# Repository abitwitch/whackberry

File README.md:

# WhackberryPi
Disconnected Cyberdeck for password management.

## Features:
- Disconnected computer (with display) with no wireless connectivity on any part of the device
- QWERTY keyboard with access to most standard symbols
- A mouse for navigating the OS in GUI mode
- A additional Micro SD card reader that can be used to create backups of passwords for storage in a secure secondary location
- A Camera to take pictures that are unable to reach the internet (useful for QR backup codes of 2FA apps)
- A disconnected microcontroller that is able to transmit data from the disconnected computer to another computer using a data diode

## How the data diode works:
1. The disconnected computer has a special command for transmitting data (`ir-sender`). This program can take standard input in bash.
2. The program encrypts the input. *NOTE* that the hardware only suport very weak and out-of-date encryption. Although it may provide a small layer of security, it should not be relied upon. This means anyone able to read the IR led blinking from inside the case, may be able to eventually decypt the messages. This seems like a low-level risk.
3. The program break the message into packets then into pulses and used the IR LED light transmit the password. Since there is no way to read messages from the LED, this is a one way communication. This is the data diode and it uses the "fire and forget" principle. This means errors in reading the message is possible. A check sum is part of the protocol to account for this possible error.
4. On the other side of the LED there is a IR Reciever. It is connected to a microcontroller that is completely disconnected* from the raspberry PI. The only way to communicate is over the air-gap via IR (one way).
*Note that the microcontroller is connected via power (5v and Ground). This allows the disconnected computer to be powered when the microcontroller is pluged into a computer. This does technically open the possibility of side channel attacks. 
5. The signal is recieved, decapsulated, combined, and de-crypted. The checksum is verified before decryption and the process will only continue if the checksum and decryption are successful.
6. When plugged into a computer, the air-gapped microcontroller acts as a keyboard and the message recieved is transmitted as keystrokes to the computer.

# Setup:
To set up a device, follow the instructions in each section of this readme from top to bottom. 

## Main Hardware
- Raspberry Pi Zero v1.3 [link](https://www.adafruit.com/product/2885)
- M5 CardKB (v1.1)
- HDMI 5" Display [link](https://www.adafruit.com/product/2232)
- Raspberry Pi Camera Module 3 [link](https://www.adafruit.com/product/5657)
- Infrared LED [link](https://www.adafruit.com/product/387)
- Infrared Receiver Sensor [link](https://www.adafruit.com/product/157)
- QT Py RP2040 [link](https://www.adafruit.com/product/4900)
- At least 1 micro CD card
- A Raspberry Pi with internet (for setup only)

## Supporting Hardware and PCB Mounting / cable accessories
- SMD Grove Female Header [link](https://www.mouser.ca/ProductDetail/Seeed-Studio/114020164?qs=7MVldsJ5Uayw%2FOfizq4F8w%3D%3D)
- USB Type-A Jack [link](https://www.mouser.ca/ProductDetail/Amphenol-FCI/87583-0010BHLF?qs=HGI6s9c03KdFNxR4%2F7F3Vg%3D%3D)
- HDMI cable [link1](https://www.adafruit.com/product/3552) [link2](https://www.adafruit.com/product/3549) [link3](https://www.adafruit.com/product/3561)
- Thru-hole 5-way Navigation switch (used as a mouse) [link](https://www.adafruit.com/product/504)
- 2x Buttons [link](https://www.adafruit.com/product/367)
- Pogo pins [link](https://www.adafruit.com/product/5381)
- Stand-off screws (the camera module may require a different size) [link](https://www.adafruit.com/product/3299)
- 1x 10k resistor [link](https://www.adafruit.com/product/2784)
- Male-male pin headers [link](https://www.adafruit.com/product/3009)
- USB Type C Breakout Board [link](https://www.adafruit.com/product/4090)
- SD card reader - SanDisk MobileMate USB 3.0 Reader [link](https://shop.sandisk.com/en-ca/products/accessories/memory-card-readers/sandisk-quickflow-microsd-usb-a-memory-card-reader?sku=SDDR-B731-GN6NN)
- DPDT switch [link](https://www.digikey.ca/en/products/detail/e-switch/EG2208/301963)
- One M4 nut and bolt (to attach CardKB)
- Solder and an soldering iron

## PCB
There PCB (Printed Circuit Board) design is included in this repository. This can be ordered online for a PCB manufacturer. If you want to forgo the case, you can order 2 boards and use the second with the one with standoffs to protect the device. 

**Schematic**

**Design view**

**Front view**

**Back view**

## Assembly guide

This guide assumes you have some experince with soldering. Locational references (up, down, left, right) assume the PCB is upright with the logo facing you. The logo side is the front of the board, the other side is the back. 
### Prepare parts
1. Break the Male-male pin headers into 2 7 pin pieces and 1 8 pin piece
2. Solder the QTpy to the two 7 pin headers with the pins facing away from the side with the USB port on it.
3. Repeat the previous step for the Raspberry Pi Zero, and USB-c Breakout board. 
4. Break the POGO pins into 2 single pins and 1 pieces with 2 still attatched pins.

### Attach USB-c Breakout board
1. Use a M2.5 hex nut as a space between the USB-c breakout board and the main PCB, with the USB-c breakour board on the back of the main PCB. Secure the breakout board in place with more M2.5 nuts and screws
2. Clip of excess pin length from the pins of the USB-c breakout board headers and then solder the pins in place

### Attach QTpy
1. Place the QTpy in place on the back of the main PCB
2. Clip of excess pin length from the pins of the QTpy headers and then solder the pins in place

### Attach Raspberry Pi Zero
1. Solder the 2 attached pogo pins below the main headed pins in the Raspberry Pi Zero footprint. The pins should be facing the back of the board
2. Use 6mm long F-F hex standoffs and screws to attach the Raspberry Pi Zero fo the back of the main PCB. The pogo pins should be making contect with the Raspberry Pi Zero, and the main header pins should slightly protrude through the main PCB. 
3. Solder all the main header pins into place.

### Other soldered-in pieces
1. Solder the GROVE Female Header onto the back of the main PCB
2. Solder the USB Type-A Jack onto the back of the main PCB
3. Insert the 5-way nav switch on the front of the PCB and solder in the pins
4. Repeat step above for both buttons below the 5-wav nav switch
5. Insert the Resistor on the back of the main PCB, clip excess pin lenth, and solder into place
6. Repeat step above for the IR-Reciever and the IR LED

### Attach the camera module
1. The mounting holes on the camera module are slightly smaller than M2.5 screws. You will either need to largen the holes are buy different hardware.
2. Use 6mm long F-F hex standoffs to attatch the camera to the back of the main PCB

### Attach CardKB
1. Use the M4 nut and bolt to attach the CardKB to the front of the main PCB

### Cables
1. Connect the Camera module to the Raspberry Pi Zero
2. Connect the CardKB to the main PCB GROVE header
3. Use the DYI HDMI cable to connect the display to the Raspberry Pi Zero

### Protection plate
Only do this if you are not making a 3D printed case
1. Choose 4 or 5 well distributed, unused, and accessible mounting holes and insert into each a M2.5 10mm Screw into an unused PCB (with nothing else solder or attached to it)
2. To the back of each of the screws, screw on a 6mm long F-F hex standoff untill snug
3. To the still protruding screws, screw on a 8mm long F-F hex standoff untill snug
4. Place the this PCB on the main on being careful not to pitch any cables
5. Screw the two boards together with M2.5 4mm Screws into the standoffs

## Setup guide

### 1.00: SD card setup
This part can be done on any trusted computer connected to the internet
1. Download Official Raspberry Pi Imager
2. Select Legacy, 32-bit - Debian Bullseye (released 2024-10-22)
3. Flash the SD card and then access the files on the SD card
4. Set up the display
   1. Setup the display. Under `bootfs > config.txt` if accessing from a SD Card reader or `\boot\config.txt` if accessing from the OS, add the following lines (more info [here](https://learn.adafruit.com/adafruit-5-800x480-tft-hdmi-monitor-touchscreen-backpack/raspberry-pi-config))
       ```
       hdmi_group=2
       hdmi_mode=87
       hdmi_cvt=800 480 60 6 0 0 0
       hdmi_drive=1
       max_usb_current=1
       ```
   2. Enable i2c. In the same `config.txt` file, uncomment "dtparam=i2c_arm=on". Follow instructions [here](https://raspberrypi.stackexchange.com/questions/83457/can-i-enable-i2c-before-first-boot)

### 2.00: Configure the OS
I suggest doing the configuartion from another pi with internet. Plug the SD card into a internet-connected Raspberry Pi and boot it. Follow the commands to set up your account and apply any updates. You can use a less secure password if you want, the more import one will be the one you use when setting up a GPG key. Reboot the device.

#### 2.01: Enable i2c
1. In terminal type, `sudo raspi-config`
2. `Interface Options > I2C > Yes  (enable) > OK > Finish`

#### 2.02: Turn on boot to terminal by default (optional)
1. In terminal type, `sudo raspi-config`
2. `System Options > Boot / Auto login > Console Autologin > Finish`
3. In subsequent boots, if you want a GUI, enter `startx` into the terminal

#### 2.03: Updrade all apps / install new apps
1. In teminal: `sudo apt update && sudo apt full-upgrade`
2. Install password manager `sudo apt-get install pass`
3. Install password manager GUI `sudo apt-get install qtpass`
4. Install a game (helpful for using the system to build up randomness) `sudo apt-get install ninvaders`
5. Install 7z for secure ziped exports: 'sudo apt-get install p7zip-full'
6. Install circuit python: `sudo pip3 install adafruit-blinka`
7. Install PyUserInput for mouse: `sudo pip3 install PyUserInput pynput`
8. Install web3 for ethereum wallet generation: `sudo pip3 install web3`

#### 2.04: Install Electum
1. Go to [https://electrum.org/#download](https://electrum.org/#download)
2. `mkdir ~/electrum`, then `cd ~/electrum`
3. Follow the instructions for "Installation from Python sources" (tested with version 4.5.8)

#### 2.05: Copy Etherium wallet script
1. `mkdir ~/cryptowallet`
2. Copy `cryptowallet/gen-eth-wallet.py` from this repo to `~/cryptowallet/gen-eth-wallet.py` on the raspberry pi
3. `chmod +x gen-eth-wallet.py`

#### 2.06: CarKB setup
1. `mkdir ~/cardkb`, then `cd ~/cardkb`
2. Follow instructions [here](https://github.com/ian-antking/cardkb) (Note: add `sudo` to `modprobe uinput`)

#### 2.07: Camera Setup
- Just plug and play
- `libcamera-hello` to test
- `libcamera-jpeg -o /path/to/file.jpg` to take a picture

#### 2.08: Set up 5-way navi mouse
1. `mkdir ~/navmouse`, then `cd ~/navmouse`
2. Copy `navmouse/mouse.py` and `navmouse/navmouselauncher.sh` from this repo to `~/navmouse` on the raspberry pi
3. `chmod +x *`
4. 'sudo nano /etc/xdg/lxsession/LXDE-pi/autostart`
5. Add this line to the end of the file, then save and exit: `@/home/{name of user}/navmouse/navmouselauncher.sh`
TODO: Fix this section

#### 2.09: Infrared Transmitter
1. Create a RAM disk for storing output:
   1. Add `newramdisk  /mnt/ramdisk  tmpfs  rw,size=8M  0  0` to `/etc/fstab` (*Note, you must replace each set of spaces with a tab*)
2. Configuration
   1. `sudo nano /boot/config.txt`
   2. Add a line with `dtoverlay=gpio-ir-tx,gpio_pin=18` to the file, then save and exit
   3. `sudo nano /etc/modules`
   4. Add a line with `lirc_dev` to the file, then save and exit
3. `mkdir ~/ir-sender`
4. Copy `ir-protocol/ir-sender` from this repo to the folder `~/ir-sender`
5. Copy `ir-protocol/ir-sender-gui` from this repo to the folder `~/Desktop/ir-sender-gui`
6. `chmod +x ~/ir-sender`
7. `chmod +x ~/Desktop/ir-sender-gui`
8. Add these lines `~/.profile`
   ```
   if [ -d "$HOME/ir-sender" ] ; then
   PATH="$PATH:$HOME/ir-sender"
   fi
   ```
9. Generate new key: `ir-sender --genkey`
10. Copy the contents of the json and use it when setting up the Infrared Reciever
11. For ease of use, add an alias for `ir-sender`
   1. Edit `~/.bashrc`
   2. Add this line to the bottom: `alias irs=ir-sender`

#### 2.10: Infrared Reciever
This part of the device is on an isolated device that emulates a keyboard when plugged into the computer.
On a PC connected to the Pico
1. Download circuit python for the QTPy RP2040 ([link](https://circuitpython.org/board/adafruit_qtpy_rp2040/)) (I used CircuitPython 9.2.6)
2. Download the circuit python bundle ([link](https://github.com/adafruit/Adafruit_CircuitPython_Bundle/releases/tag/20250319)) (I used 'March 19, 2025 auto-release')
3. While holding down the `BOOT` button on the QTPy, connect it to the PC.
4. Copy the "uf2" file you downloaded in step 1 to the device. You should see `INDEX.HTM` and `INFO_UF2.TXT` there already. Wait for the device to reboot.
5. Unzip the folder from step 2 and copy the following folders and file to the `lib` folder of the QTPy.
   `adafruit_hid`, `adafruit_pixelbuf.mpy`, `neopixel.mpy`, `adafruit_rsa`, `adafruit_logging.mpy`, `adafruit_binascii`, `adafruit_hashlib` 
8. Copy the contents of the `ir-receiver-code.py` to `code.py`
9. Copy `boot.py` to `boot.py` at the top level of the QTPy
10. Create a new file at the top level called `private_key.json` and put the json contents in it generated when setting up the Infrared Transmitter

Optional: If you want a second reciever for any reason (for example, you don't want to plug the same reciever into every computer you need a password on), here's how to set up a secondary one.
1. Buy a secondary RP2040 device. This guide will assume you're using [the Waveshare RP2040-One](https://www.waveshare.com/product/rp2040-one.htm).
2. Solder on a IR (Infrared) Receiver (the same one listed earlier in this project). Attach GND to GND, V to 3.3V, and OUT to GP0. 
3. Follow the same steps above (for the main Infrared Reciever), with these minor changes
   1. In the `code.py` file, change `board.MOSI` to `board.GP0` and `board.NEOPIXEL` to `board.GP16`
   2. In the `boot.py` file, change `board.A0` to `board.GP15`
   3. Copy the `private_key.json` from the original RP2040 device to this one

#### 2.11: Copy over the utility scripts
1. `mkdir ~/utilities`
2. Copy `utilities/exportbackup.sh` from this repo to `~/utilities/exportbackup.sh` on the raspberry pi
3. Copy `utilities/importfromcsv.py` from this repo to `~/utilities/importfromcsv.py` on the raspberry pi
4. `sudo chmod +x ~/utilities/*`

#### 2.12: Test the system
1. Power down the raspberry pi you're using for setup. Move the SD card to the offline raspberry pi. 
2. Test the system to make sure all features work as expected

#### 2.12: Copy any passwords to the SD card
Copy password from any existing password managers to the SD Card (make sure to place them in a appropriate folder as not to mess up the OS on the SD Card).

### 3.00: Finish system init (offline) 
Only perform these steps when you're done setting up the device and ready to never connected to the internet again
1. If the SD card is still in the Raspberry Pi you were using for setup, move it to the offline Raspberry Pi Zero. 
2. Use system for 5-10 minutes to generate entopy (try `ninvaders`)
3. `mkdir ~/mydata`
4. Set up password manager
   1. Generate key
      1. `gpg --gen-key`
      2. Real name: user
      3. Email: [empty]
      4. `O` for okay
      5. Enter a password (this will be the master password for the password manager). Make sure it is a secure password and do not share it. 
      6. Note the id of the key. This will be a lond alphanumberic sequence right above "uid"
   2. Set key to never expire
      1. `gpg --edit-key key-id-as-noted-above`
      2. `expire`
      3. enter `0`
      4. `q` to quit (and `y` to save changes)
   2. `pass init key-id-as-noted-above`
5. Generate Bitcoin BTC wallet
   1. Start electrum with this command `~/electrum/Electrum-4.5.8/run_electrum`
   2. This application will run slowly. Be prepared to wait a few minutes between screens.
   3. Follow prompts and be sure to save the new seed to the password manager (`pass`). Using a password is recommended, you can generate and store one it `pass`, then copy it to the clipboard by using `pass -c {Folder/name}`
   4. In the "Recieve" tab, create a never expiring request and save the public address to `pass` as well. You can use this to send money to the wallet.
   5. Export the private keeys to `pass`
      1. Under "Wallet" > "Private keys", select "Export"
      2. Specify the file location to somewhere on `/mnt/ramdisk` (this way it will not presist on disk as plain text)
      3. Add a column to the CSV titled "BurntPrivKey", and set it to "No" for all rows
      4. Run `cat /mnt/ramdisk/{filename-of-exported-keys.csv} | pass insert {Folder/name} -m`
6. Generate Etherium ETH wallet
   1. Run the command `python3 ~/cryptowallet/gen-eth-wallet.py`
   2. Enter both the private key and the public key to the `pass` password manager

## Using the system
**Basic commands**
- To start the GUI for the OS: `startx`

**Password manager**
- To add a password: `pass insert path/to/name`
- To find a password: `pass find name`
- To generate a password: `pass generate path/to/name`
- To find a password: `pass find myaccount`
- To add metadata: `pass insert path/to/name.meta` (there are other oiptions, this is just a suggestion)
- To send a password to the QT py, `pass show path/to/name | irs`
- To edit a password, `pass edit path/to/name`
- To use the password manager gui: `qtpass`

**Saving a encrypted image**
1. Take a picture `libcamera-jpeg -o /mnt/ramdisk/imagename.jpg` *note, raw image will not persist on reboot
2. Encrypt the image `gpg -e -r key-id-as-noted-above /mnt/ramdisk/imagename.jpg -o ~/mydata/imagename.jpg.gpg`

**Viewing a encrypted image**
1. Decrypt the image `gpg -d ~/mydata/imagename.jpg.gpg -o /mnt/ramdisk/imagename.jpg`
2. View the image here `/mnt/ramdisk/imagename.jpg` *note, image will not persist on reboot

**Creating a full backup**
This is meant to act as either an off site backup or a way to share all your data.
1. Safely procure a un-used micro SD card. This will prevent any contamination of your disconnected system.
2. Create a backup. Run the script under `~/utilities/exportbackup.sh`
3. Follow the prompts. Note that with a lot of passwords, the "Exporting passwords" step can take a long time to run (last time was ~30 minutes for me).
4. Copy or move the resulting file to the SD Card.

**Import csv to password manager**
1. Modify the script here: `~/utilities/importfromcsv.py` to match the fields in the CSV from your password manager
2. Run `python3 ~/utilities/importfromcsv.py /path/to/passwords.csv`
3. After successfully importing the passwords, delete the csv `rm /path/to/passwords.csv`

## Sending recieving Bitcoin (btc)
You can send and recieve btc without exposing your private keys to the internet.

### Recieving:
1. Open Electrum
2. Go to the recieving tab and create a request. Make one of your "burnt" addresses it not being used. Send btc using any app to that address.

### Sending:
Option 1: signing a transaction (requires manual transcription)
1. On a computer connected to the internet
   1. Install Electrum and wait for it to sync
   2. Go to File > New/Restore
   3. Select "Import Bitcoin addresses or private keys"
   4. Enter the public addess (NOT the private keys!) from the Whackberry device (you can do that using this command: `echo bitcoin_public_address | irs`)
   5. Under the send tab, enter the address you want to send to, the amount, then click "Pay..."
   6. Set the transation fee and click "OK"
   7. Click the share button and "Copy to clipboard..." (paste in a text editor)
2. On the Whackberry
   1. Open Electrum
   2. On the top menu, "Tools" > "Load transation" > "From text"
   3. The camera will not work with the Electrum app, so you will have to manually copy the transation to the whackberry (make no mistakes, good luck).
   4. "Sign" the transation
   5. Click the share button and "Copy to clipboard..." (recommend pasting it somewhere like `/mnt/ramdisk/txn.txt`)
   6. Transfer that file back to the internet connected computer: `cat /mnt/ramdisk/txn.txt | irs` (you'll want to open a text editor on the internet connected computer to capture the contents of the file) 
3. On a computer connected to the internet
   1. In Electrum, on the top menu, "Tools" > "Load transation" > "From text"
   2. Paste in the transation contents you transfered from the whackberry.
   3. Click "Broadcast"
Option 2: Burning a Private key
1. Mark the private key as "burnt" on the Whackberry: `pass edit path/to/privatekeys`. I recommend labeling it in the Electrum GUI too (under the addresses tab)
2. Copy the ONLY THE BURNT private keys to a internet connected computer
   1. Test a command to ONLY get the burnt addresses: `pass show path/to/privatekeys | grep ,Yes` (Make 100% sure it's only outputing the private keys you want to burn)
   2. Copy the ket to the internet connected computer: ``pass show path/to/privatekeys | grep ,Yes | irs`
3. On the internet connected computer
   1. Follow steps 1.1 to 1.3 under "Option 1"
   2. Enter the private key
   3. Transfer all the bitcoin to your intended addresses. Keep in mind you can also transfer to other addresses on the Whackberry that are not yet burnt.

## Accessing cold wallets (online) 
1. Use `ir-sender` to send the target private key from the disconnected raspberry pi to a computer connect to the internet. Make sure to note any private keys or seeds being transfered. They are no longer totaly secure.
2. For Bitcion BTC:
   1. Download and install the Electrum application. Be very careful to download from the offical page (https://electrum.org/#download)[https://electrum.org/#download]
   2. Open the application and when prompted, select "Standard wallet" then "I already have a seed"
   3. Enter the seed for the Bitcoin BTC wallet.
   4. You can use the "Send" tab to send to any address. Start with a small amount to make sure everything is working.
3. For Etherium ETH:
   1. You can use any wallet that supports importing private keys to access the BTC. I'll include instructions for MetaMask Firefox Extension (v12.6.2) below.
   2. Go to MetaMask's site. Be sure it's the official source: [https://metamask.io/download/](https://metamask.io/download/)
   3. Download and lauch the extension
   4. Follow the propmts and select "create new wallet"
   5. Once on the main account page, click the account dropdown at the top of the screen
   6. Select "Add account or hardware wallet" then "Import account"
   7. Enter the private key for Etherium ETH.
   8. You can use the "Send" button to send to any address. Start with a small amount to make sure everything is working.

## Case
There is a 3D printable case included in this repository to help manage the cables and protect the devices. This case is yet to be printed and tested, so it likely we need to be altered and iterated. 

**Front of case**

**Back of case**

## Trouble shooting
- Opening the camera causes the system to crash
   - This is likely a power issue to the camera. First try adding these two lines to the "/boot/config.txt" file; `over_voltage=2` and `force_turbo=1`. If the problem persists, lower the blacklight one the display by cutting the trace in between the two pads labeled "Open for -25mA" (more info [here](https://learn.adafruit.com/adafruit-5-800x480-tft-hdmi-monitor-touchscreen-backpack/pinouts)).

## Future work
- setup HID to act as a security key
- fix tempermental QTpy

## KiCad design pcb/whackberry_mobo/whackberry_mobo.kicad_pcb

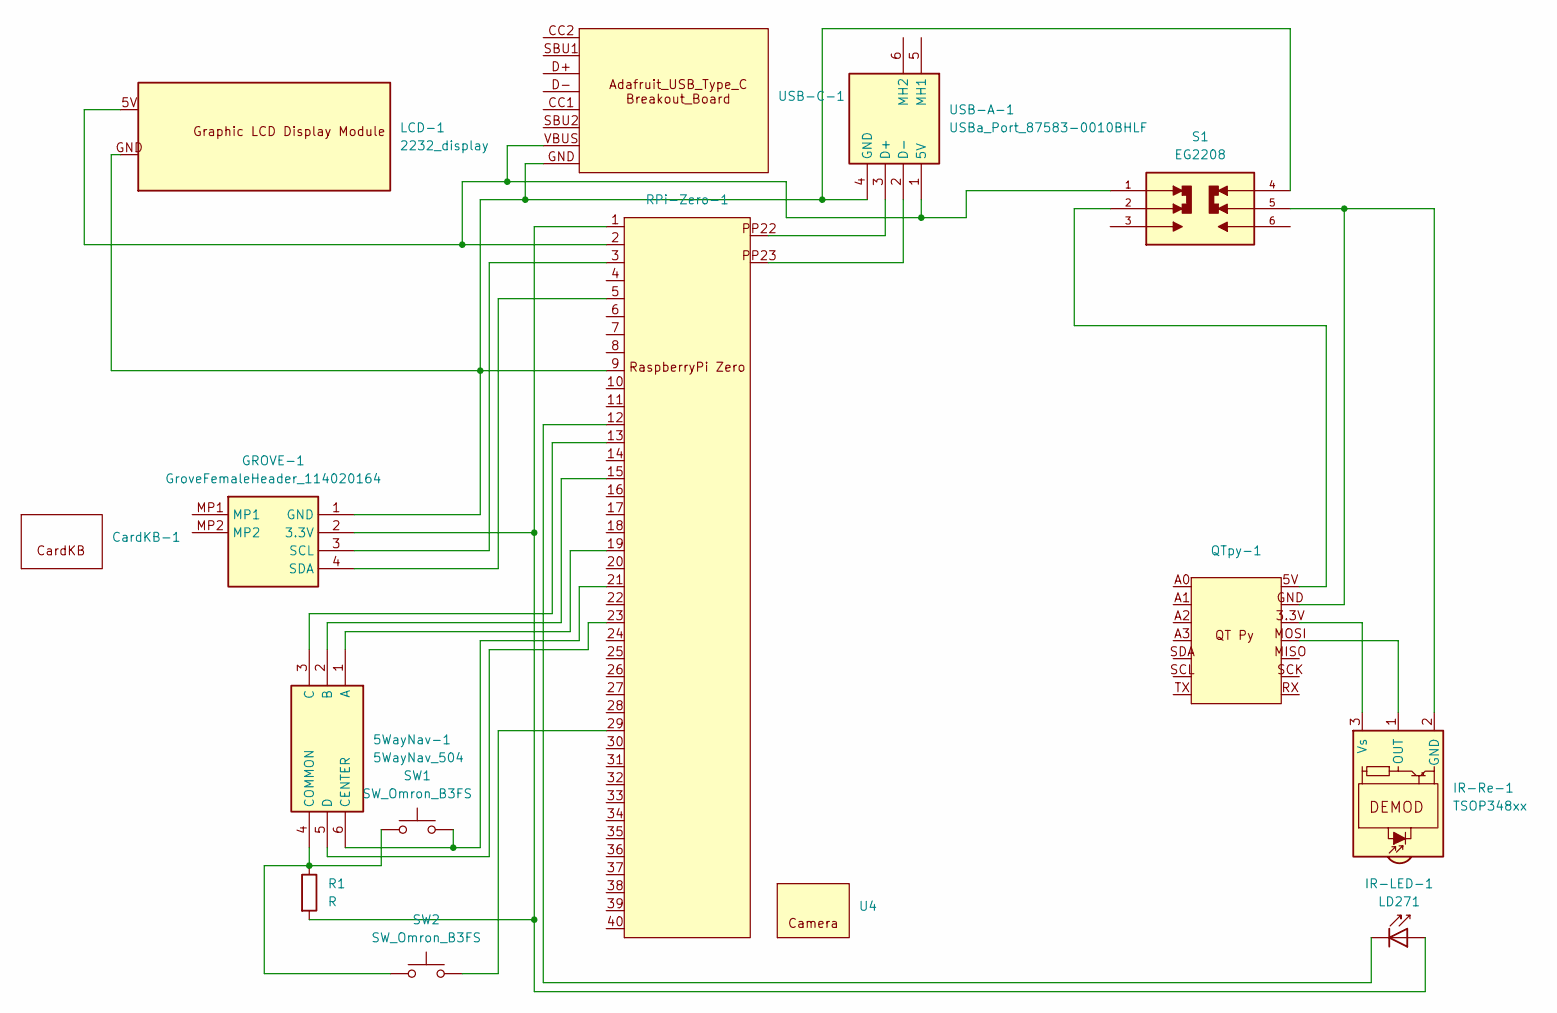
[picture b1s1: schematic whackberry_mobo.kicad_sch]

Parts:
5WayNav-1: 5WayNav_504; Mouser Part Number 485-504
CardKB-1: CardKB
GROVE-1: GroveFemaleHeader_114020164; Mouser Part Number 713-114020164
IR-LED-1: LD271; LED_D5.0mm_IRGrey
IR-Re-1: TSOP348xx; Vishay_MOLD-3Pin
LCD-1: 2232_display; Display_MODULE_2232; PARTREV N/A
QTpy-1: QT_Py
R1: R; R_Axial_DIN0207_L6.3mm_D2.5mm_P10.16mm_Horizontal
RPi-Zero-1: Modified_Raspberry_Pi_Zero_Socketed_THT_FaceDown_MountingHo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
S1: EG2208; SW_EG2208; PARTREV C
SW1, SW2: SW_Omron_B3FS; SW_TH_Tactile_Omron_B3F-10xx
U4: Camera
USB-A-1: USBa_Port_87583-0010BHLF; USBa_Port_875830010BHLF; Manufacturer_Part_Number 87583-0010BHLF
USB-C-1: Adafruit_USB_Type_C_Breakout_Board

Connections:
unnamed: 5WayNav-1.1 (A), RPi-Zero-1.19
unnamed: 5WayNav-1.2 (B), RPi-Zero-1.15
unnamed: 5WayNav-1.3 (C), RPi-Zero-1.13
unnamed: 5WayNav-1.6 (CENTER), RPi-Zero-1.21, SW1.2
unnamed: 5WayNav-1.4 (COMMON), R1.1, SW1.1, SW2.1
unnamed: 5WayNav-1.5 (D), RPi-Zero-1.23
unnamed: GROVE-1.2 (3.3V), IR-LED-1.2 (A), R1.2, RPi-Zero-1.1
unnamed: GROVE-1.1 (GND), LCD-1.GND, RPi-Zero-1.9, S1.4, USB-A-1.4 (GND), USB-C-1.GND
unnamed: GROVE-1.3 (SCL), RPi-Zero-1.3
unnamed: GROVE-1.4 (SDA), RPi-Zero-1.5
unnamed: IR-LED-1.1 (K), RPi-Zero-1.12
unnamed: IR-Re-1.2 (GND), QTpy-1.GND, S1.5
unnamed: IR-Re-1.1 (OUT), QTpy-1.MOSI
unnamed: IR-Re-1.3 (Vs), QTpy-1.3.3V
unnamed: QTpy-1.5V, S1.2
unnamed: RPi-Zero-1.29, SW2.2
unnamed: LCD-1.5V, RPi-Zero-1.2, S1.1, USB-A-1.1 (5V), USB-C-1.VBUS
unnamed: RPi-Zero-1.PP22, USB-A-1.3 (D+)
unnamed: RPi-Zero-1.PP23, USB-A-1.2 (D-)

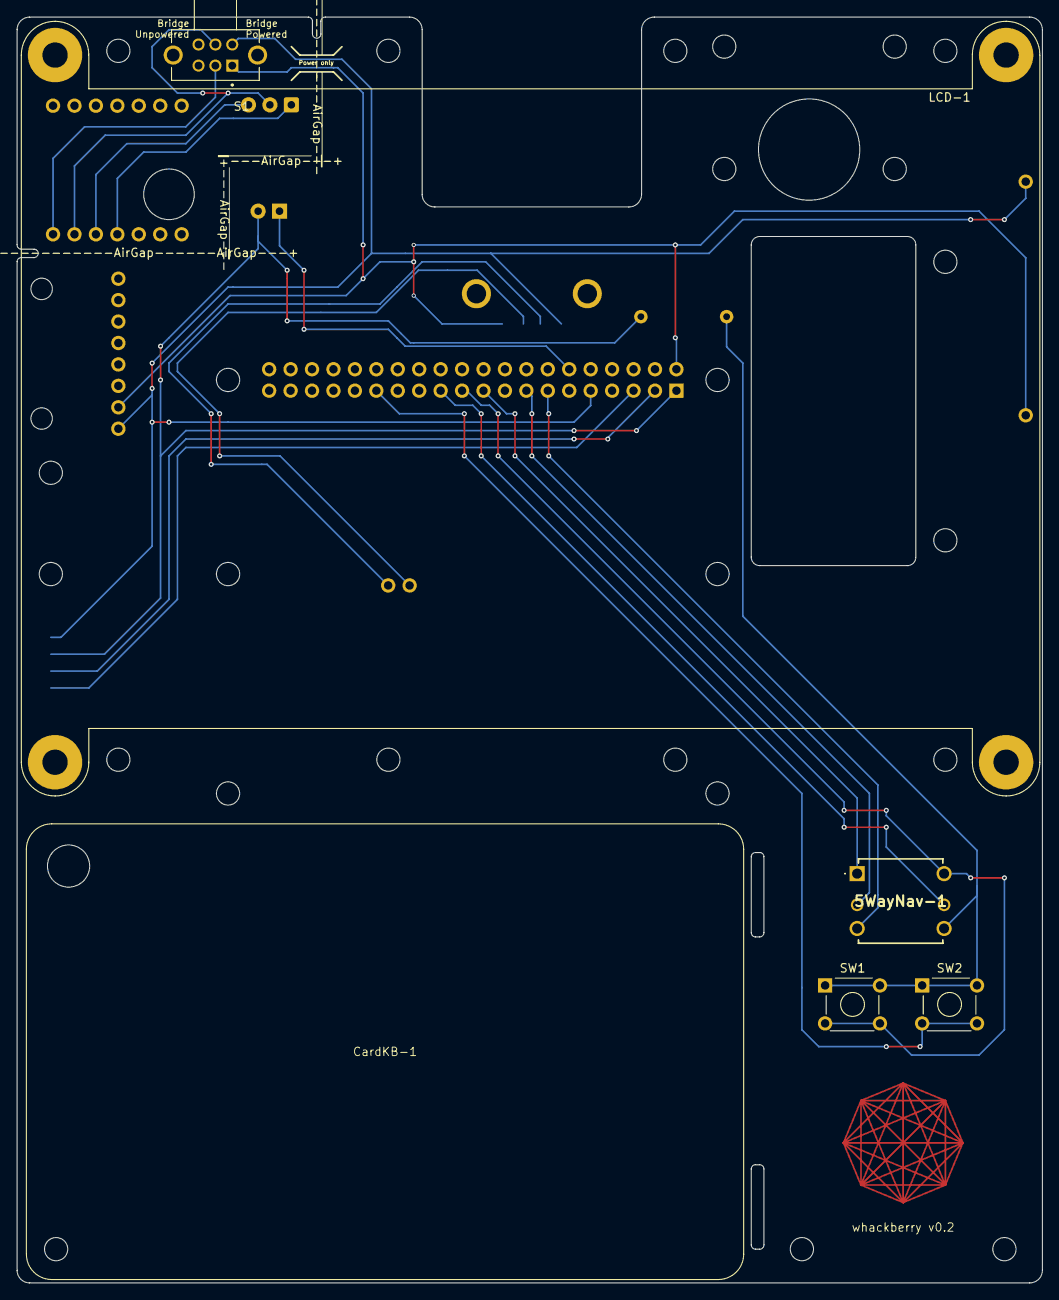
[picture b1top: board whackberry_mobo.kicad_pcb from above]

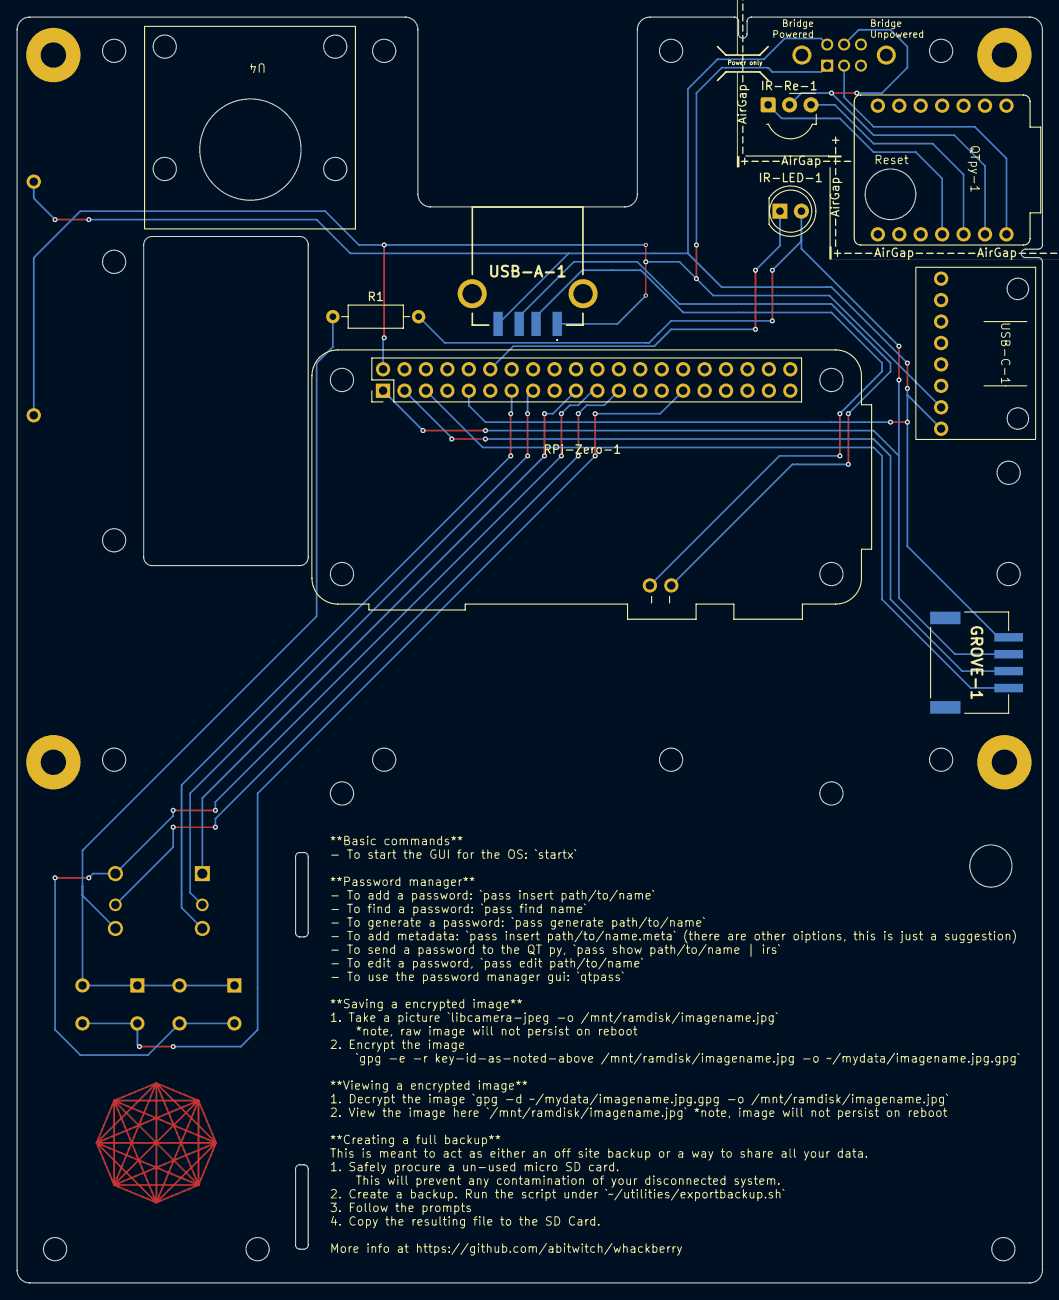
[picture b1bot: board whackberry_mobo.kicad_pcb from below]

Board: 2 copper layers, 121.5 x 150.0 mm, 15 parts (9 on the bottom side), 19 nets.

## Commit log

2025-01-01 Update hardware-idea
2025-03-08 adding exploration notes
2025-03-08 playing with sender and reciever
2025-03-08 send and receive working
2025-03-16 mouse working on gui start
2025-03-30 Updates to sender.py from rpi
2025-03-30 Updates to receiver.py from rpi
2025-04-06 Moving private key to separate file
2025-04-06 Update .gitignore to ignore privatekeys
2025-04-08 ir-sender and ir-receiver Update README.md
2025-04-08 Create ir-sender
2025-04-12 starting kicad project for pcb
2025-04-16 adding kicad project
2025-04-18 more kicad work
2025-04-18 another kicad work save
2025-04-18 adding last batch of symbols and footprints in KiCad
2025-04-19 placing parts on PCB
2025-04-19 Ready for tracing PCB
2025-04-19 More changes before tracing PCB
2025-04-19 adding gerber files
2025-04-20 adding images of PCB
2025-04-30 new pbc changes, fixes to ir-receiver, start on wallet maker
2025-05-03 fixing mapping mouse pins
2025-05-03 starting work on case
2025-05-04 case work
2025-05-04 stop tracking backups
2025-05-06 case work, adding bump outs
2025-05-07 case work, building slider
2025-05-17 case work and cryptowallet exploration
2025-05-19 more case work
2025-05-20 case work. almost done first draft
2025-05-23 case work, adding long keybard supports
2025-05-29 adding reset button hole
2025-05-31 adding cable mgnt and screwdriver slot
2025-06-01 casework: adding measurements and camera hole
2025-06-01 casework: adding measurements and fixes. Ready for 1st print draft.
2025-06-01 untested mouse changes and crypto exploration
2025-06-04 adding print layout option to case and minor fixes
2025-06-06 got crypto wallet solution, cleaning repo and docs
2025-06-08 improving documenation
2025-06-08 adding export capability
2025-06-11 fixing time out feature
2025-06-12 work on import utility
2025-06-12 New PCB changes(v0.2)
2025-06-13 Update ir-sender to allow for different user names
2025-06-13 Fixing problems with README.md during walkthrough
2025-06-15 fixes from another setup run through
2025-06-20 fixed typo
2025-07-08 adding hole to access QTpy Reset button
2026-01-24 Adding a control switch for bridge power and other pcb improvements
2026-01-24 Adding small note to readme
2026-01-24 adding notes to README for a optional second reciever
2026-02-20 disable mass storage device on rp2040
2026-02-23 adding notes to btc wallet guide
2026-03-01 adding note to README
2026-03-23 adding notes on sending/recieving btc
